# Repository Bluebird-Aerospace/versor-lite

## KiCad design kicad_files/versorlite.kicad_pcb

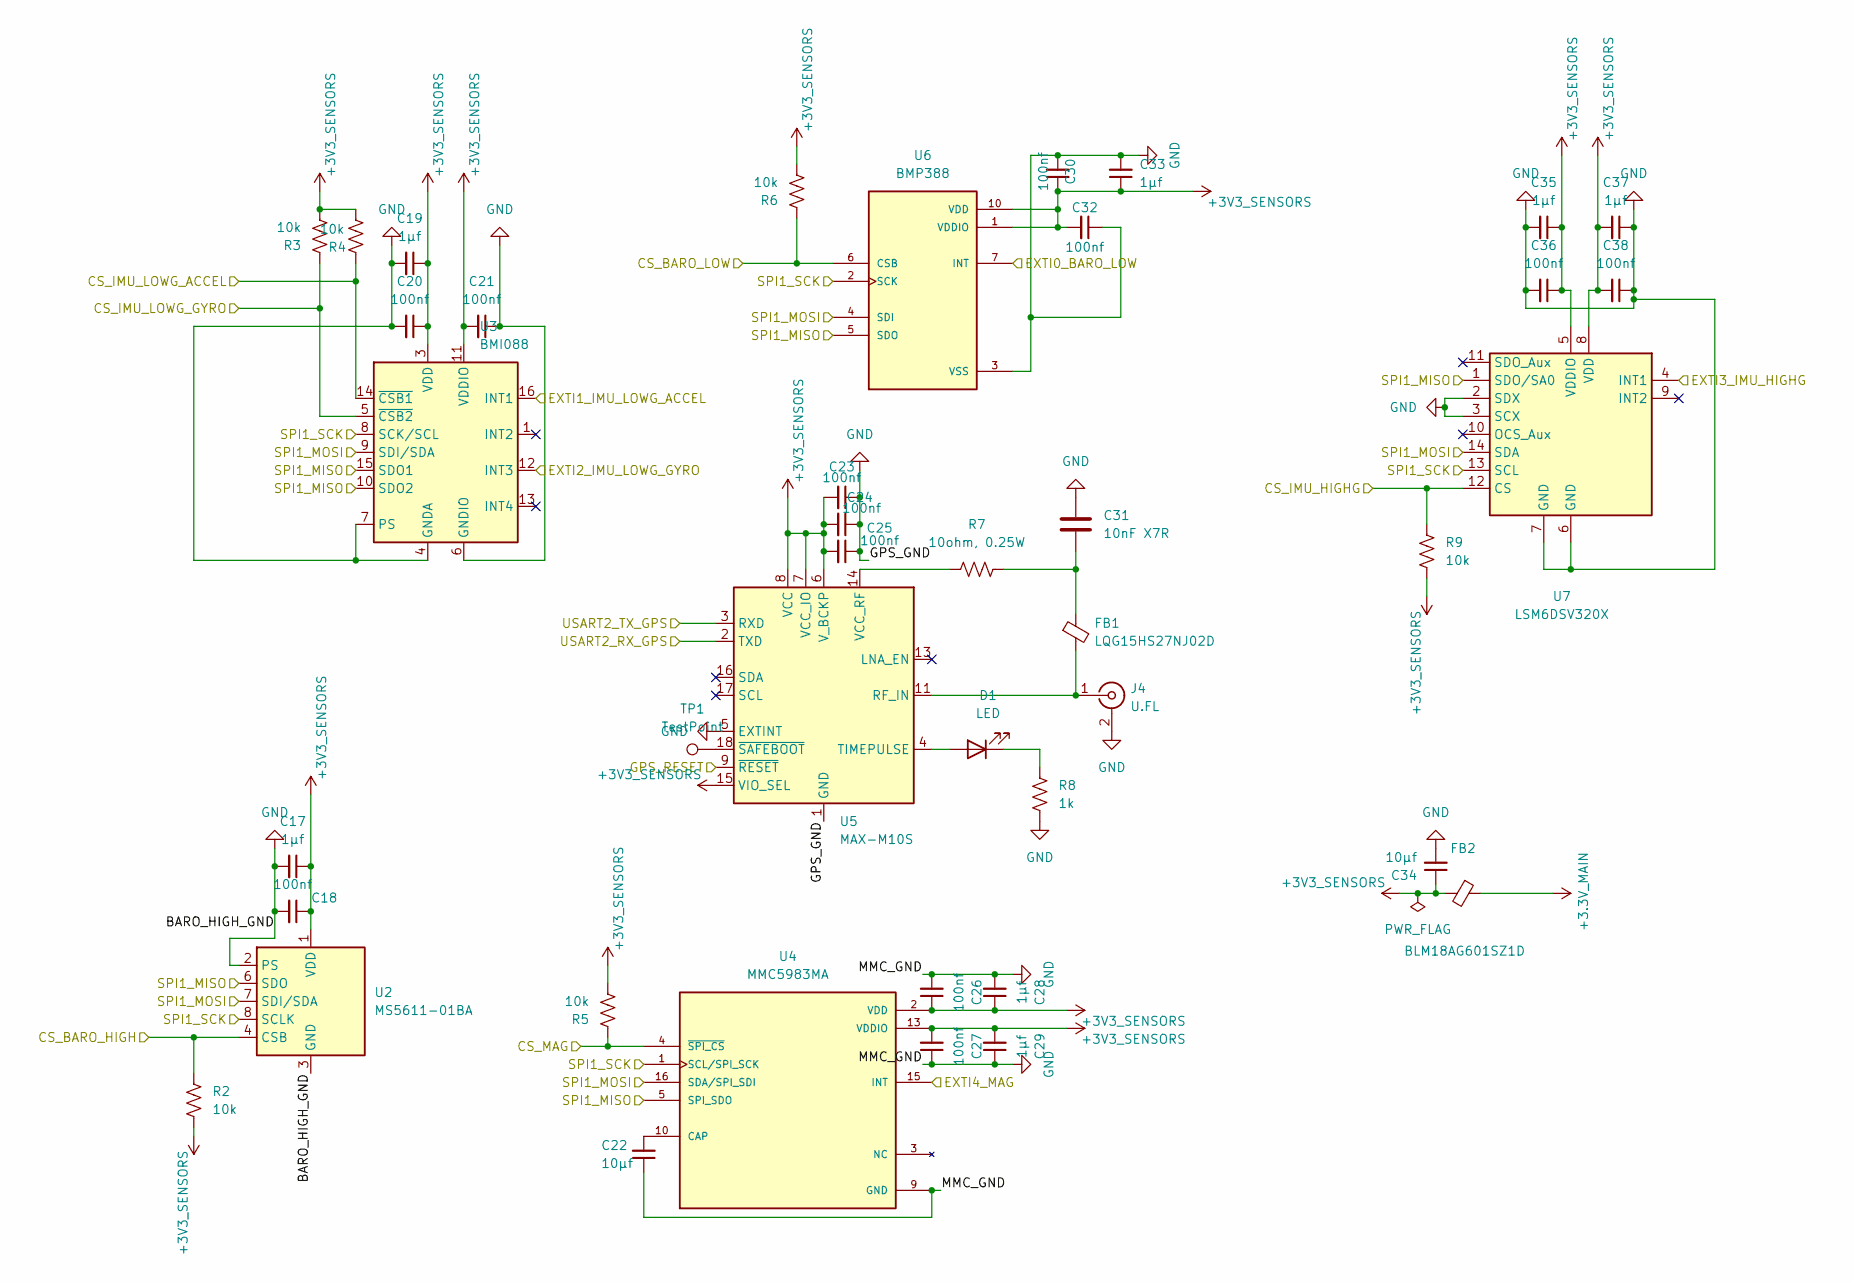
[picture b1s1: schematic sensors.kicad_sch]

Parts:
C17, C19, C28, C29, C33, C35, C37: 1μf; C_0402_1005Metric
C18, C20, C21, C23, C24, C25, C26, C27, C30, C32, C36, C38: 100nf; C_0402_1005Metric
C22, C34: 10μf; C_0805_2012Metric
C31: 10nF X7R; C_0402_1005Metric
D1: LED; LED_0603_1608Metric
FB1: LQG15HS27NJ02D; L_0402_1005Metric
FB2: BLM18AG601SZ1D; L_0603_1608Metric
J4: U.FL; U.FL_Hirose_U.FL-R-SMT-1_Vertical; LCSC C5137195
R2, R3, R4, R5, R6, R9: 10k; R_0402_1005Metric
R7: 10ohm, 0.25W; R_1206_3216Metric
R8: 1k; R_0603_1608Metric
TP1: TestPoint; TestPoint_Pad_D1.0mm
U2: MS5611-01BA; LGA-8_3x5mm_P1.25mm
U3: BMI088; Bosch_LGA-16_4.5x3mm_P0.5mm_LayoutBorder7x1y_ClockwisePinNu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
U4: MMC5983MA; PQFN50P300X300X100-16N; PARTREV A
U5: MAX-M10S; ublox_MAX
U6: BMP388; PARTREV 1.1
U7: LSM6DSV320X; LGA-14_3x2.5mm_P0.5mm_LayoutBorder3x4y

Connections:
+3.3V_MAIN: FB2.1; also elsewhere on the board
+3V3_SENSORS: C17.1, C18.1, C19.1, C20.1, C21.2, C23.2, C24.2, C25.2, C26.1, C27.2, C28.1, C29.2, C30.1, C32.2, C33.1, C34.1, C35.1, C36.1, C37.2, C38.2, FB2.2, R2.2, R3.2, R4.2, R5.2, R6.2, R9.2, U2.1 (VDD), U3.3 (VDD), U3.11 (VDDIO), U4.2 (VDD), U4.13 (VDDIO), U5.6 (V_BCKP), U5.7 (VCC_IO), U5.8 (VCC), U5.15 (VIO_SEL), U6.1 (VDDIO), U6.10 (VDD), U7.5 (VDDIO), U7.8 (VDD)
/MCU/CS_BARO_HIGH: R2.1, U2.4 (CSB), U2.5 (CSB); also elsewhere on the board
/MCU/CS_BARO_LOW: R6.1, U6.6 (CSB); also elsewhere on the board
/MCU/CS_IMU_HIGHG: R9.1, U7.12 (CS); also elsewhere on the board
/MCU/CS_IMU_LOWG_ACCEL: R4.1, U3.14 (~CSB1); also elsewhere on the board
/MCU/CS_IMU_LOWG_GYRO: R3.1, U3.5 (~CSB2); also elsewhere on the board
/MCU/CS_MAG: R5.1, U4.4 (~SPI_CS); also elsewhere on the board
/MCU/EXTI0_BARO_LOW: U6.7 (INT); also elsewhere on the board
/MCU/EXTI1_IMU_LOWG_ACCEL: U3.16 (INT1); also elsewhere on the board
/MCU/EXTI2_IMU_LOWG_GYRO: U3.12 (INT3); also elsewhere on the board
/MCU/EXTI3_IMU_HIGHG: U7.4 (INT1); also elsewhere on the board
/MCU/EXTI4_MAG: U4.15 (INT); also elsewhere on the board
/MCU/GPS_RESET: U5.9 (~RESET); also elsewhere on the board
/MCU/SPI1_MISO: U2.6 (SDO), U3.10 (SDO2), U3.15 (SDO1), U4.5 (SPI_SDO), U6.5 (SDO), U7.1 (SDO/SA0); also elsewhere on the board
/MCU/SPI1_MOSI: U2.7 (SDI/SDA), U3.9 (SDI/SDA), U4.16 (SDA/SPI_SDI), U6.4 (SDI), U7.14 (SDA); also elsewhere on the board
/MCU/SPI1_SCK: U2.8 (SCLK), U3.8 (SCK/SCL), U4.1 (SCL/SPI_SCK), U6.2 (SCK), U7.13 (SCL); also elsewhere on the board
/MCU/USART2_RX_GPS: U5.2 (TXD); also elsewhere on the board
/MCU/USART2_TX_GPS: U5.3 (RXD); also elsewhere on the board
GND: C17.2, C18.2, C19.2, C20.2, C21.1, C22.1, C23.1, C24.1, C25.1, C26.2, C27.1, C28.2, C29.1, C30.2, C31.1, C32.1, C33.2, C34.2, C35.2, C36.2, C37.1, C38.1, J4.2 (Ext), R8.2, U2.2 (PS), U2.3 (GND), U3.2 (GNDA), U3.4 (GNDA), U3.6 (GNDIO), U3.7 (PS), U4.9 (GND), U4.11 (GND), U5.1 (GND), U5.5 (EXTINT), U5.10 (GND), U5.12 (GND), U6.3 (VSS), U6.8 (VSS), U6.9 (VSS), U7.2 (SDX), U7.3 (SCX), U7.6 (GND), U7.7 (GND); also elsewhere on the board
unnamed: C31.2, FB1.1, R7.2
unnamed: D1.2 (A), U5.4 (TIMEPULSE)
unnamed: D1.1 (K), R8.1
unnamed: FB1.2, J4.1 (In), U5.11 (RF_IN)
unnamed: C22.2, U4.10 (CAP)
unnamed: R7.1, U5.14 (VCC_RF)
unnamed: TP1.1 (1_1), U5.18 (~SAFEBOOT)

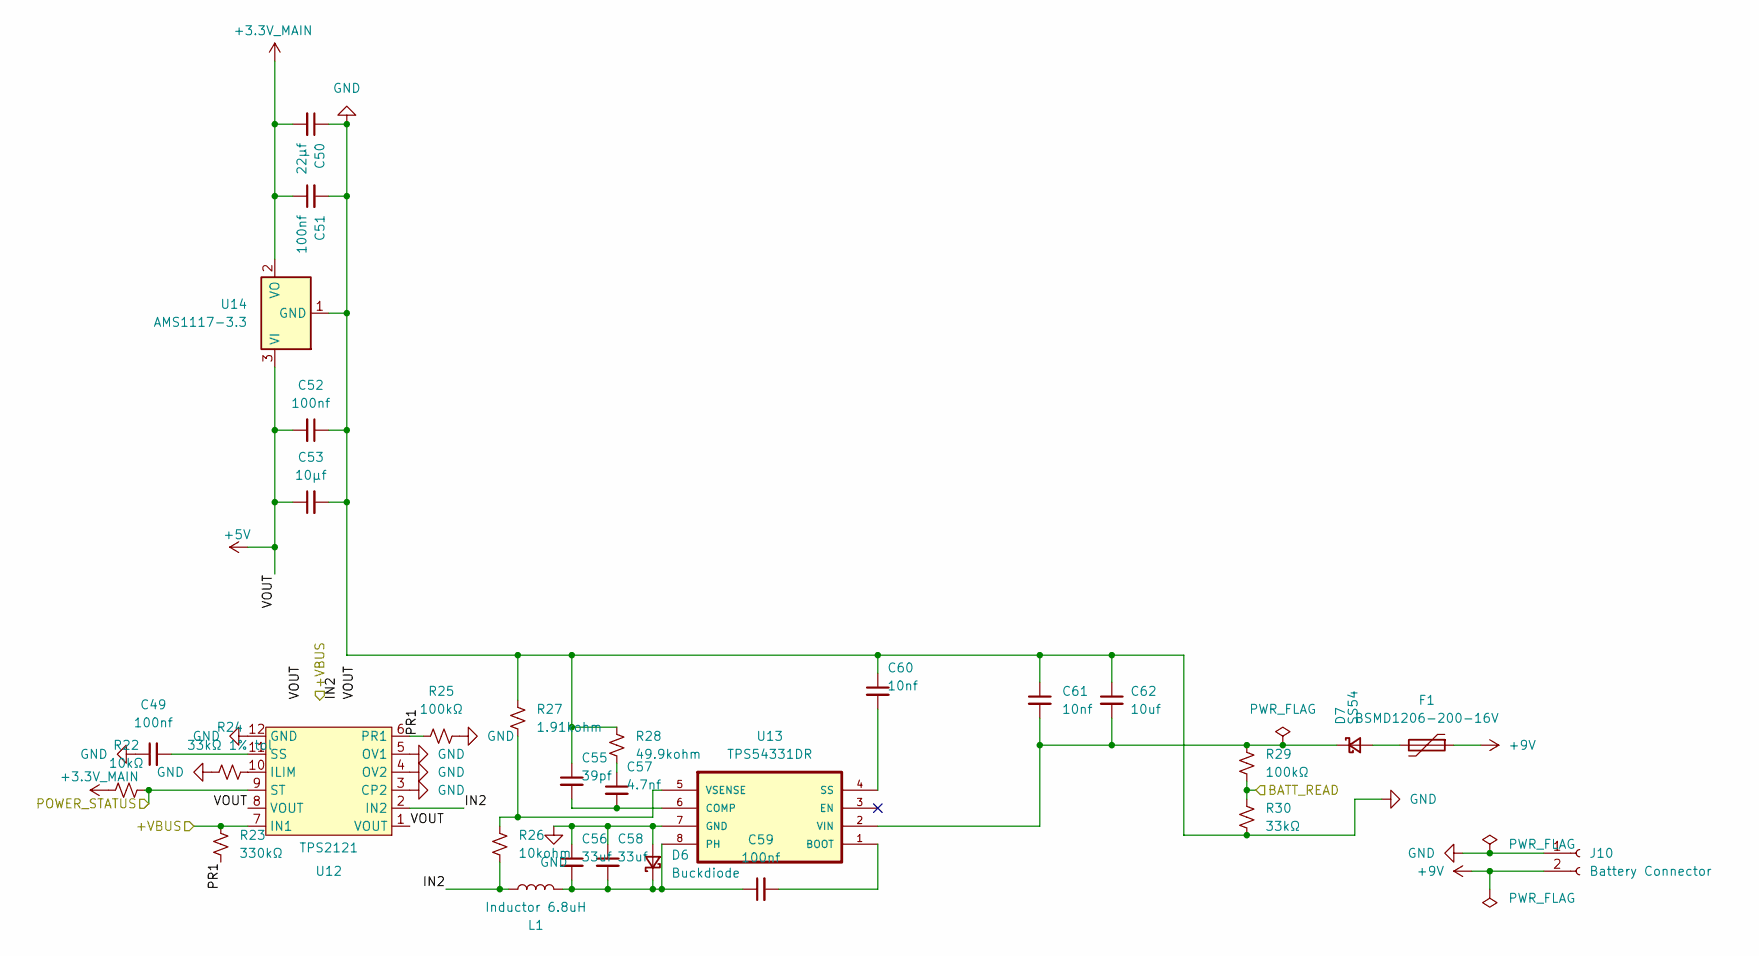
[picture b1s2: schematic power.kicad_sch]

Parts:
C49, C51, C52, C59: 100nf; C_0402_1005Metric
C50: 22μf; C_0805_2012Metric
C53: 10μf; C_0805_2012Metric
C55: 39pf; C_0402_1005Metric
C56, C58: 33uf; C_0805_2012Metric
C57: 4.7nf; C_0402_1005Metric
C60, C61: 10nf; C_0402_1005Metric
C62: 10uf; C_0805_2012Metric
D6: Buckdiode; D_SMA
D7: SS54; D_SMA
F1: BSMD1206-200-16V; Fuse_1206_3216Metric
J10: Battery Connector; AMASS_XT30U-F_1x02_P5.0mm_Vertical
L1: Inductor 6.8uH; L_Coilcraft_XxL4030
R22: 10kΩ; R_0402_1005Metric
R23: 330kΩ; R_0402_1005Metric
R24: 33kΩ 1% tol; R_0402_1005Metric
R25: 100kΩ; R_0402_1005Metric
R26: 10kohm; R_0402_1005Metric
R27: 1.91kohm; R_0402_1005Metric
R28: 49.9kohm; R_0402_1005Metric
R29: 100kΩ; R_0603_1608Metric
R30: 33kΩ; R_0603_1608Metric
U12: TPS2121; IC_TPS2121RUXR
U13: TPS54331DR; SOIC127P599X175-8N
U14: AMS1117-3.3; SOT-223-3_TabPin2

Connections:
+3.3V_MAIN: C50.2, C51.1, R22.1, U14.2 (VO); also elsewhere on the board
+5V: C52.2, C53.1, U12.1 (VOUT), U12.1_1 (TV), U12.8 (VOUT), U12.8_1 (TV), U14.3 (VI); also elsewhere on the board
+9V: F1.1, J10.2; also elsewhere on the board
/MCU/BATT_READ: R29.2, R30.1; also elsewhere on the board
/MCU/POWER_STATUS: R22.2, U12.9 (ST); also elsewhere on the board
/Power/+VBUS: R23.2, U12.7 (IN1), U12.7_1 (TV); also elsewhere on the board
/Power/IN2: L1.1, R26.2, U12.2 (IN2), U12.2_1 (TV)
/Power/PR1: R23.1, R25.1, U12.6 (PR1)
GND: C49.1, C50.1, C51.2, C52.1, C53.2, C55.1, C56.1, C58.1, C60.1, C61.1, C62.1, D6.2 (A), J10.1, R24.1, R25.2, R27.1, R28.1, R30.2, U12.3 (CP2), U12.4 (OV2), U12.5 (OV1), U12.12 (GND), U13.7 (GND), U14.1 (GND); also elsewhere on the board
unnamed: C57.1, R28.2
unnamed: C56.2, C58.2, C59.1, D6.1 (K), L1.2, U13.8 (PH)
unnamed: D7.2 (A), F1.2
unnamed: C61.2, C62.2, D7.1 (K), R29.1, U13.2 (VIN)
unnamed: R24.2, U12.10 (ILIM)
unnamed: C49.2, U12.11 (SS)
unnamed: C59.2, U13.1 (BOOT)
unnamed: C55.2, C57.2, U13.6 (COMP)
unnamed: C60.2, U13.4 (SS)
unnamed: R26.1, R27.2, U13.5 (VSENSE)

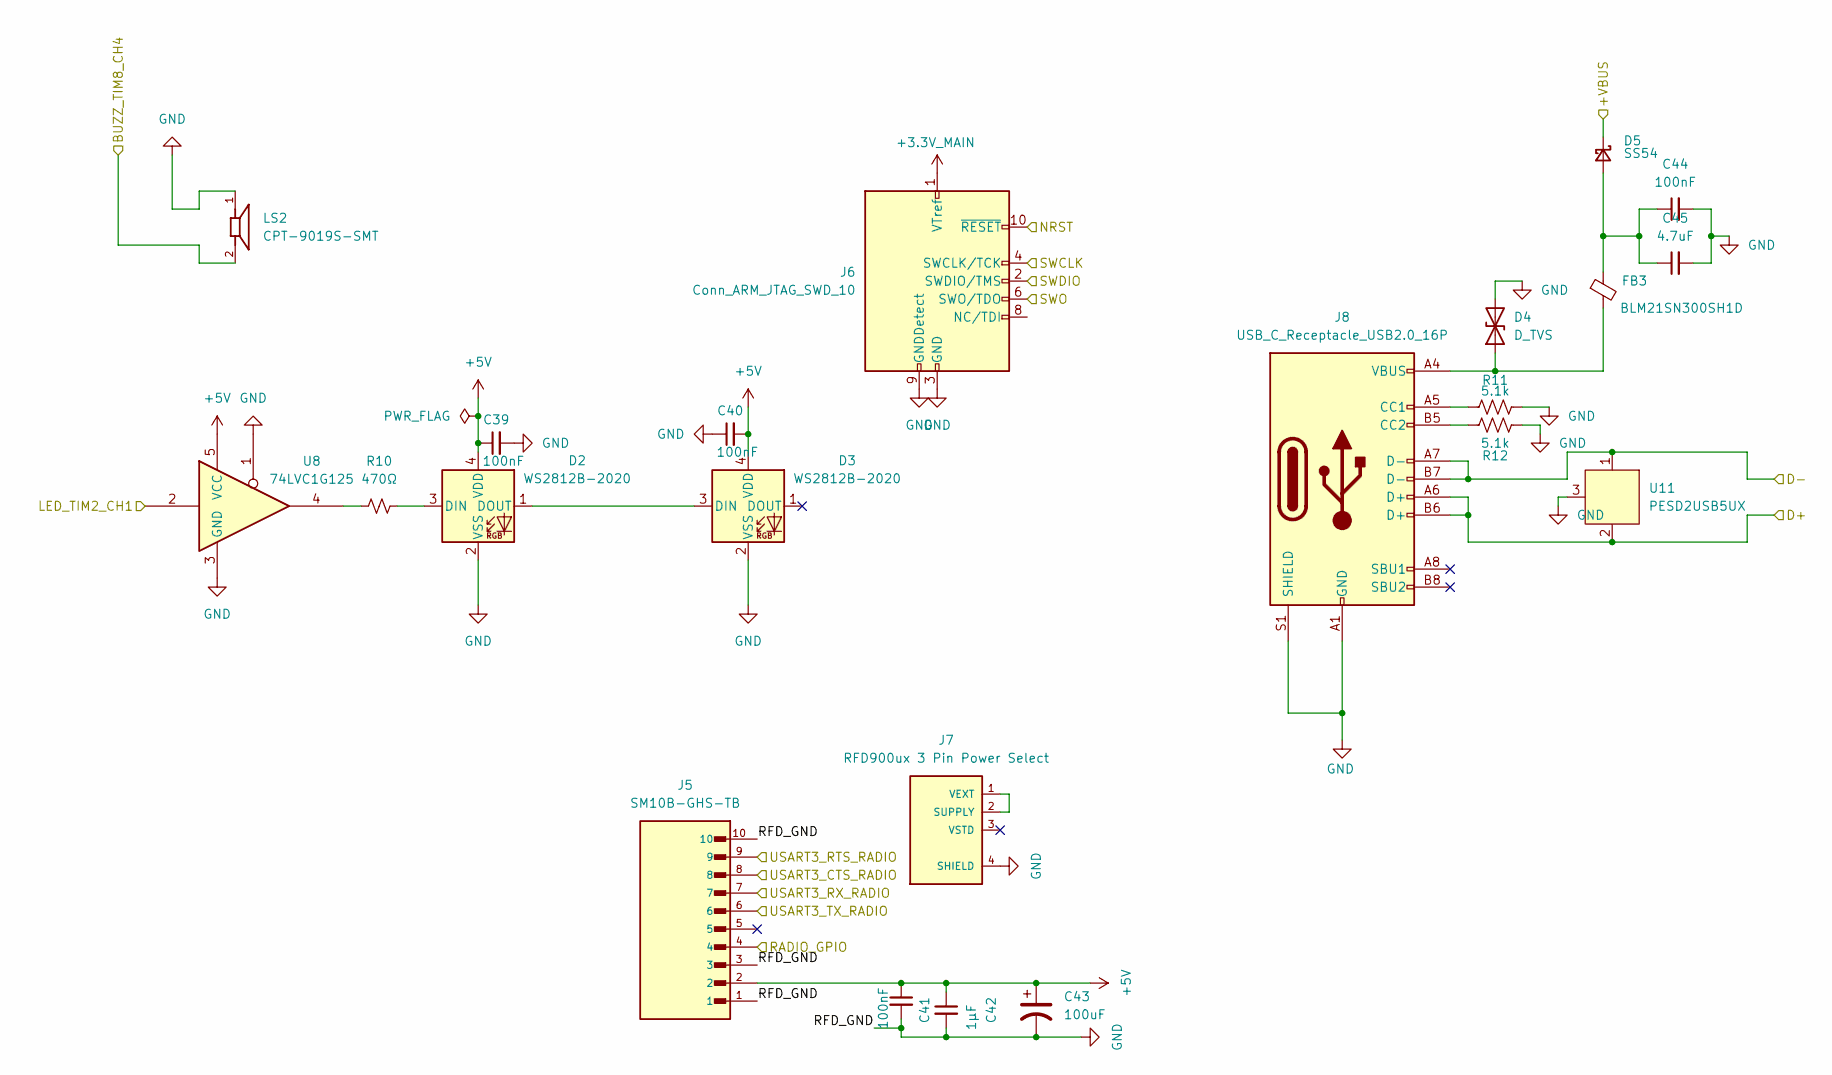
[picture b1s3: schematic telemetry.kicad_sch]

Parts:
C39, C40, C41, C44: 100nF; C_0402_1005Metric
C42: 1μF; C_0402_1005Metric
C43: 100uF; CP_EIA-3528-21_Kemet-B
C45: 4.7uF; C_0603_1608Metric
D2, D3: WS2812B-2020; LED_WS2812B-2020_PLCC4_2.0x2.0mm
D4: D_TVS; D_SOD-882
D5: SS54; D_SMA
FB3: BLM21SN300SH1D; L_0805_2012Metric
J5: SM10B-GHS-TB; JST_SM10B-GHS-TB
J6: Conn_ARM_JTAG_SWD_10; PinHeader_2x05_P1.27mm_Vertical
J7: RFD900ux 3 Pin Power Select; CONN_BM03B-GHS-TBT_LF__SN__N_
J8: USB_C_Receptacle_USB2.0_16P; USB_C_Receptacle_GCT_USB4105-xx-A_16P_TopMnt_Horizontal
LS2: CPT-9019S-SMT; CUI_CPT-9019S-SMT; PART_REV 1.0
R10: 470Ω; R_0402_1005Metric
R11, R12: 5.1k; R_0402_1005Metric
U8: 74LVC1G125; SOT-23-5
U11: PESD2USB5UX; TSOT-23

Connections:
+3.3V_MAIN: J6.1 (VTref); also elsewhere on the board
+5V: C39.1, C40.2, C41.1, C42.1, C43.1, D2.4 (VDD), D3.4 (VDD), J5.2, U8.5 (VCC); also elsewhere on the board
/MCU/BUZZ_TIM8_CH4: LS2.2; also elsewhere on the board
/MCU/D+: J8.A6 (D+), J8.B6 (D+), U11.2; also elsewhere on the board
/MCU/D-: J8.A7 (D-), J8.B7 (D-), U11.1; also elsewhere on the board
/MCU/LED_TIM2_CH1: U8.2; also elsewhere on the board
/MCU/NRST: J6.10 (~RESET); also elsewhere on the board
/MCU/RADIO_GPIO: J5.4; also elsewhere on the board
/MCU/SWCLK: J6.4 (SWCLK/TCK); also elsewhere on the board
/MCU/SWDIO: J6.2 (SWDIO/TMS); also elsewhere on the board
/MCU/SWO: J6.6 (SWO/TDO); also elsewhere on the board
/MCU/USART3_CTS_RADIO: J5.8; also elsewhere on the board
/MCU/USART3_RTS_RADIO: J5.9; also elsewhere on the board
/MCU/USART3_RX_RADIO: J5.7; also elsewhere on the board
/MCU/USART3_TX_RADIO: J5.6; also elsewhere on the board
/Power/+VBUS: D5.1 (K); also elsewhere on the board
GND: C39.2, C40.1, C41.2, C42.2, C43.2, C44.2, C45.2, D2.2 (VSS), D3.2 (VSS), D4.2 (A2), J5.1, J5.3, J5.10, J6.3 (GND), J6.5 (GND), J6.9 (GNDDetect), J7.4 (SHIELD), J7.5 (SHIELD), J8.A1 (GND), J8.A12 (GND), J8.B1 (GND), J8.B12 (GND), J8.S1 (SHIELD), LS2.1, R11.2, R12.2, U8.1, U8.3 (GND), U11.3; also elsewhere on the board
unnamed: D2.3 (DIN), R10.2
unnamed: D2.1 (DOUT), D3.3 (DIN)
unnamed: D4.1 (A1), FB3.2, J8.A4 (VBUS), J8.A9 (VBUS), J8.B4 (VBUS), J8.B9 (VBUS)
unnamed: C44.1, C45.1, D5.2 (A), FB3.1
unnamed: J7.1 (VEXT), J7.2 (SUPPLY)
unnamed: J8.A5 (CC1), R11.1
unnamed: J8.B5 (CC2), R12.1
unnamed: R10.1, U8.4

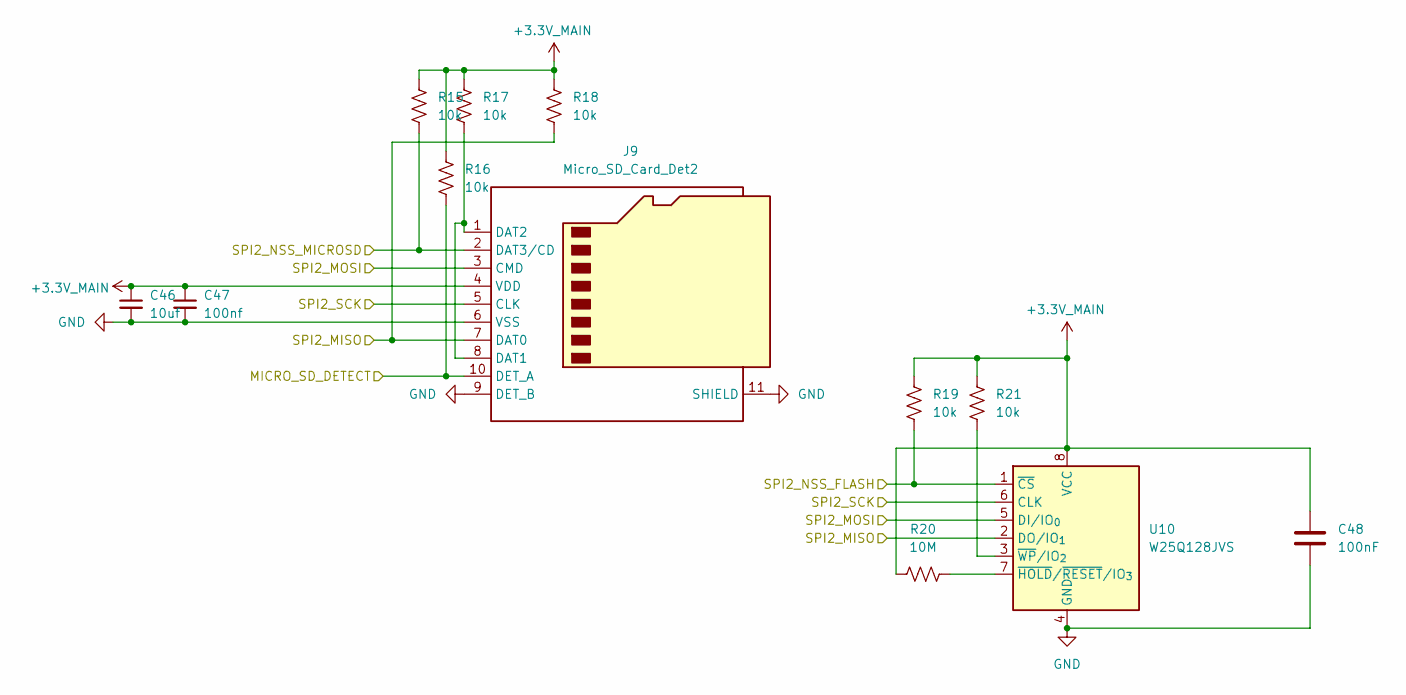
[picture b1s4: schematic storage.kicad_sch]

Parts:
C46: 10uf; C_0805_2012Metric
C47: 100nf; C_0402_1005Metric
C48: 100nF; C_0402_1005Metric
J9: Micro_SD_Card_Det2; microSD_HC_Molex_104031-0811
R15, R16, R17, R18, R19, R21: 10k; R_0402_1005Metric
R20: 10M; R_0603_1608Metric
U10: W25Q128JVS; SOIC-8_5.3x5.3mm_P1.27mm

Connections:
+3.3V_MAIN: C46.1, C47.1, C48.1, J9.4 (VDD), R15.1, R16.1, R17.2, R18.2, R19.1, R20.1, R21.1, U10.8 (VCC); also elsewhere on the board
/MCU/MICRO_SD_DETECT: J9.10 (DET_A), R16.2; also elsewhere on the board
/MCU/SPI2_MISO: J9.7 (DAT0), R18.1, U10.2 (DO/IO_{1}); also elsewhere on the board
/MCU/SPI2_MOSI: J9.3 (CMD), U10.5 (DI/IO_{0}); also elsewhere on the board
/MCU/SPI2_NSS_FLASH: R19.2, U10.1 (~CS); also elsewhere on the board
/MCU/SPI2_NSS_MICROSD: J9.2 (DAT3/CD), R15.2; also elsewhere on the board
/MCU/SPI2_SCK: J9.5 (CLK), U10.6 (CLK); also elsewhere on the board
GND: C46.2, C47.2, C48.2, J9.6 (VSS), J9.9 (DET_B), J9.11 (SHIELD), U10.4 (GND); also elsewhere on the board
unnamed: J9.1 (DAT2), J9.8 (DAT1), R17.1
unnamed: R20.2, U10.7 (~HOLD/~RESET/IO_{3})
unnamed: R21.2, U10.3 (~WP/IO_{2})

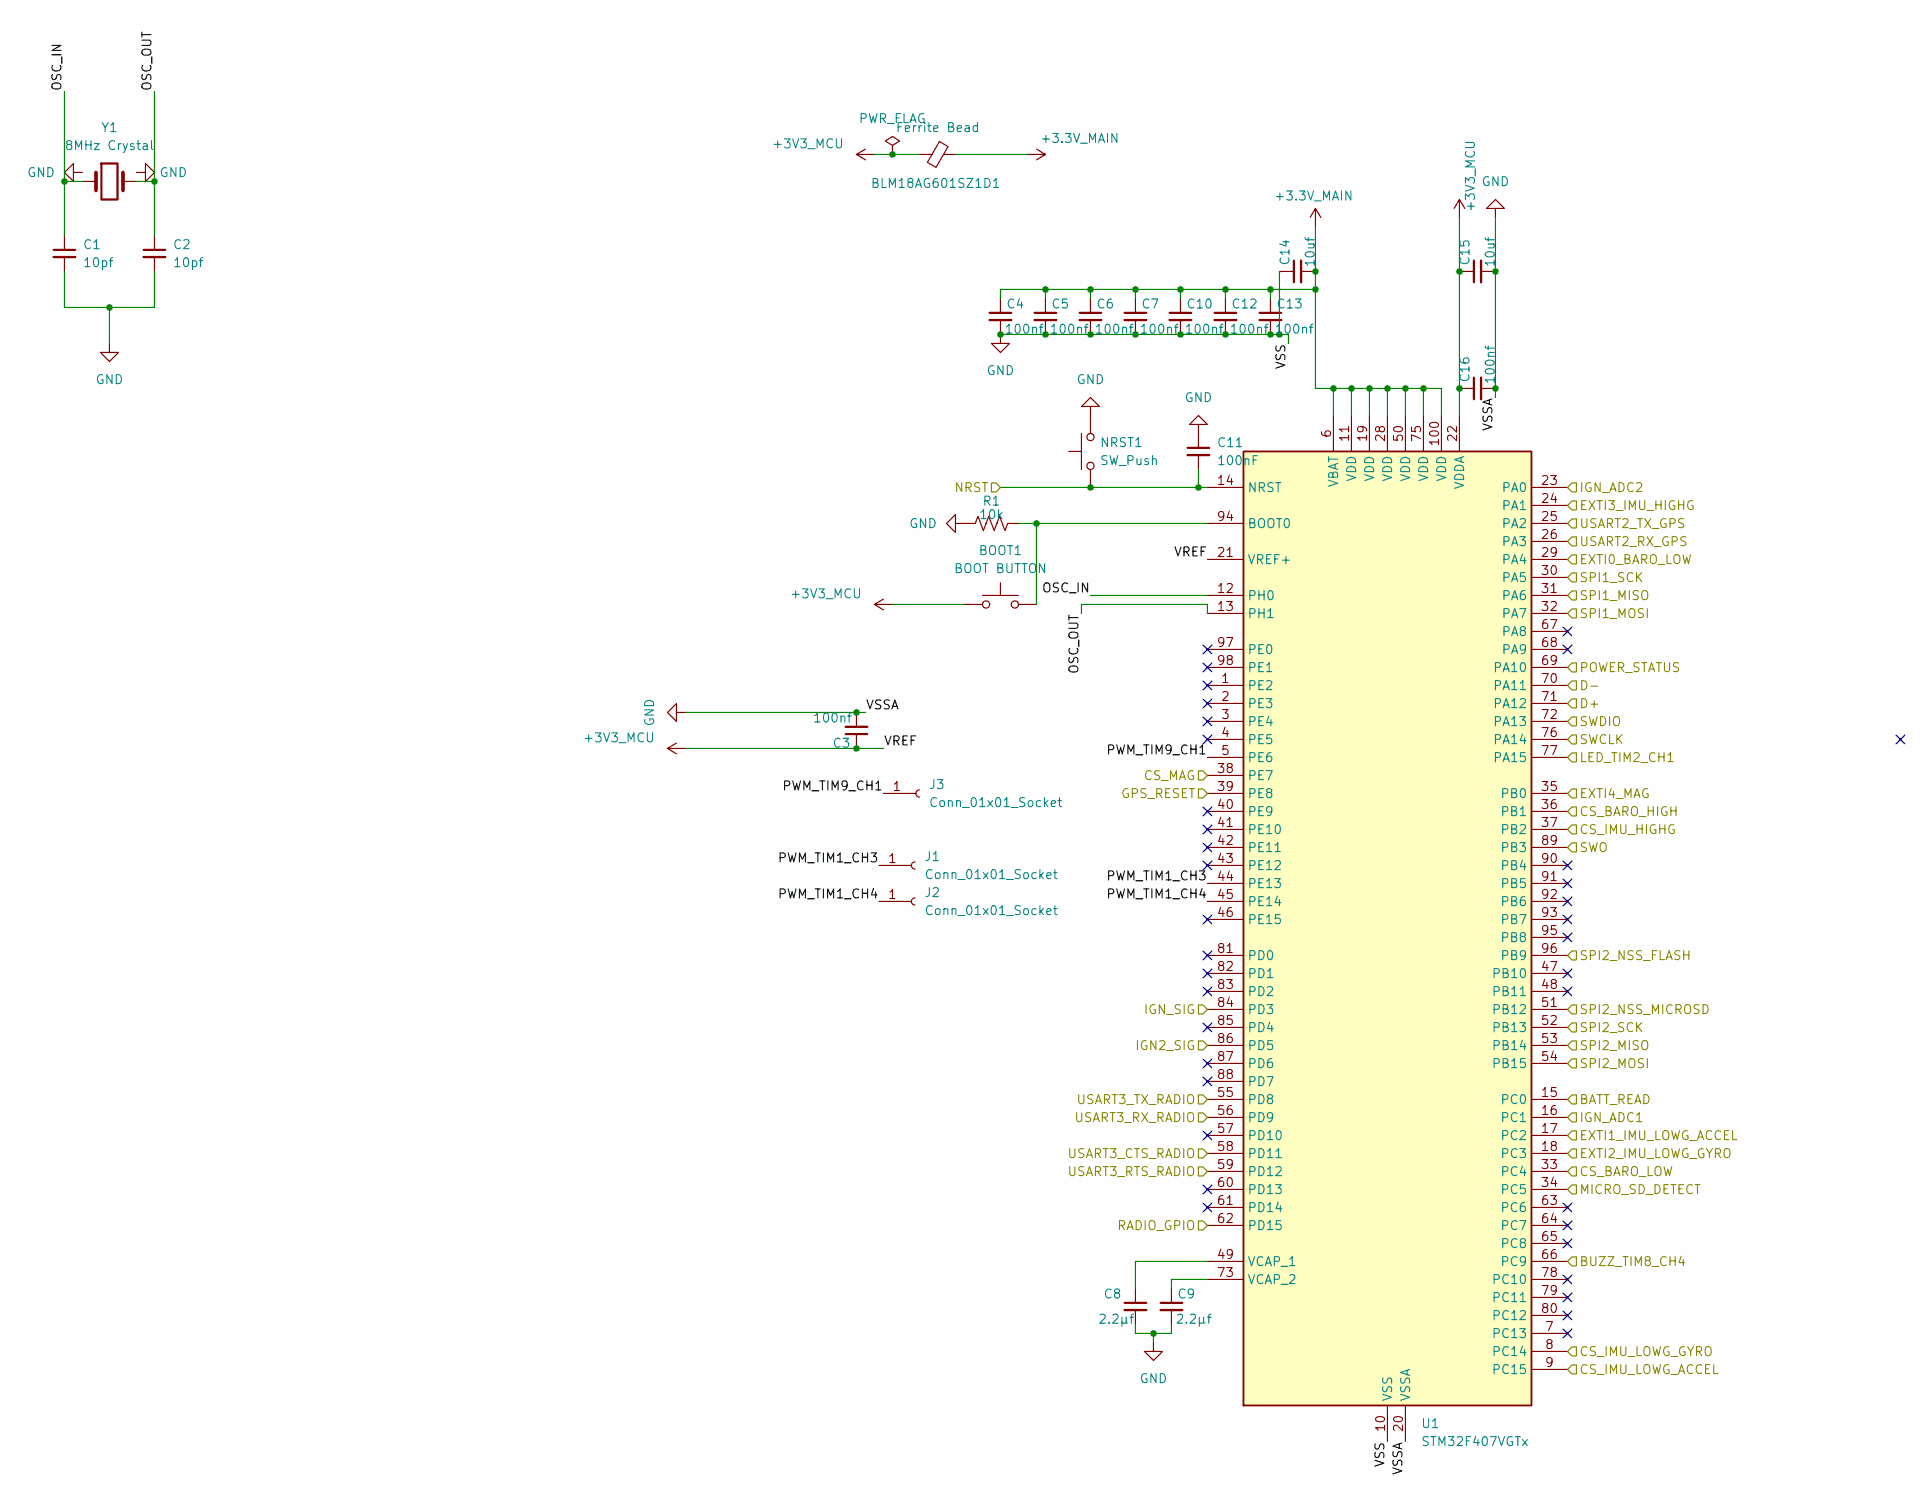
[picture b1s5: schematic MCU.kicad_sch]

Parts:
BLM18AG601SZ1D1: Ferrite Bead; L_0603_1608Metric
BOOT1: BOOT BUTTON; SW_SPST_PTS810
C1, C2: 10pf; C_0402_1005Metric
C3, C4, C5, C6, C7, C10, C12, C13, C16: 100nf; C_0402_1005Metric
C8, C9: 2.2µf; C_0603_1608Metric
C11: 100nF; C_0402_1005Metric
C14, C15: 10uf; C_0805_2012Metric
J1, J2, J3: Conn_01x01_Socket; SolderWire-0.5sqmm_1x01_D0.9mm_OD2.1mm
NRST1: SW_Push; SW_SPST_PTS810
R1: 10k; R_0402_1005Metric
U1: STM32F407VGTx; LQFP-100_14x14mm_P0.5mm
Y1: 8MHz Crystal; Crystal_SMD_3225-4Pin_3.2x2.5mm

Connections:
+3.3V_MAIN: BLM18AG601SZ1D1.1, C4.1, C5.1, C6.1, C7.1, C10.1, C12.1, C13.1, C14.2, U1.6 (VBAT), U1.11 (VDD), U1.19 (VDD), U1.28 (VDD), U1.50 (VDD), U1.75 (VDD), U1.100 (VDD); also elsewhere on the board
+3V3_MCU: BLM18AG601SZ1D1.2, BOOT1.1, C3.1, C15.1, C16.1, U1.21 (VREF+), U1.22 (VDDA)
/MCU/BATT_READ: U1.15 (PC0); also elsewhere on the board
/MCU/BUZZ_TIM8_CH4: U1.66 (PC9); also elsewhere on the board
/MCU/CS_BARO_HIGH: U1.36 (PB1); also elsewhere on the board
/MCU/CS_BARO_LOW: U1.33 (PC4); also elsewhere on the board
/MCU/CS_IMU_HIGHG: U1.37 (PB2); also elsewhere on the board
/MCU/CS_IMU_LOWG_ACCEL: U1.9 (PC15); also elsewhere on the board
/MCU/CS_IMU_LOWG_GYRO: U1.8 (PC14); also elsewhere on the board
/MCU/CS_MAG: U1.38 (PE7); also elsewhere on the board
/MCU/D+: U1.71 (PA12); also elsewhere on the board
/MCU/D-: U1.70 (PA11); also elsewhere on the board
/MCU/EXTI0_BARO_LOW: U1.29 (PA4); also elsewhere on the board
/MCU/EXTI1_IMU_LOWG_ACCEL: U1.17 (PC2); also elsewhere on the board
/MCU/EXTI2_IMU_LOWG_GYRO: U1.18 (PC3); also elsewhere on the board
/MCU/EXTI3_IMU_HIGHG: U1.24 (PA1); also elsewhere on the board
/MCU/EXTI4_MAG: U1.35 (PB0); also elsewhere on the board
/MCU/GPS_RESET: U1.39 (PE8); also elsewhere on the board
/MCU/IGN2_SIG: U1.86 (PD5); also elsewhere on the board
/MCU/IGN_ADC1: U1.16 (PC1); also elsewhere on the board
/MCU/IGN_ADC2: U1.23 (PA0); also elsewhere on the board
/MCU/IGN_SIG: U1.84 (PD3); also elsewhere on the board
/MCU/LED_TIM2_CH1: U1.77 (PA15); also elsewhere on the board
/MCU/MICRO_SD_DETECT: U1.34 (PC5); also elsewhere on the board
/MCU/NRST: C11.2, NRST1.1, U1.14 (NRST); also elsewhere on the board
/MCU/OSC_IN: C1.1, U1.12 (PH0), Y1.1
/MCU/OSC_OUT: C2.1, U1.13 (PH1), Y1.3
/MCU/POWER_STATUS: U1.69 (PA10); also elsewhere on the board
/MCU/PWM_TIM1_CH3: J1.1 (Pin_1_1), U1.44 (PE13)
/MCU/PWM_TIM1_CH4: J2.1 (Pin_1_1), U1.45 (PE14)
/MCU/PWM_TIM9_CH1: J3.1 (Pin_1_1), U1.5 (PE6)
/MCU/RADIO_GPIO: U1.62 (PD15); also elsewhere on the board
/MCU/SPI1_MISO: U1.31 (PA6); also elsewhere on the board
/MCU/SPI1_MOSI: U1.32 (PA7); also elsewhere on the board
/MCU/SPI1_SCK: U1.30 (PA5); also elsewhere on the board
/MCU/SPI2_MISO: U1.53 (PB14); also elsewhere on the board
/MCU/SPI2_MOSI: U1.54 (PB15); also elsewhere on the board
/MCU/SPI2_NSS_FLASH: U1.96 (PB9); also elsewhere on the board
/MCU/SPI2_NSS_MICROSD: U1.51 (PB12); also elsewhere on the board
/MCU/SPI2_SCK: U1.52 (PB13); also elsewhere on the board
/MCU/SWCLK: U1.76 (PA14); also elsewhere on the board
/MCU/SWDIO: U1.72 (PA13); also elsewhere on the board
/MCU/SWO: U1.89 (PB3); also elsewhere on the board
/MCU/USART2_RX_GPS: U1.26 (PA3); also elsewhere on the board
/MCU/USART2_TX_GPS: U1.25 (PA2); also elsewhere on the board
/MCU/USART3_CTS_RADIO: U1.58 (PD11); also elsewhere on the board
/MCU/USART3_RTS_RADIO: U1.59 (PD12); also elsewhere on the board
/MCU/USART3_RX_RADIO: U1.56 (PD9); also elsewhere on the board
/MCU/USART3_TX_RADIO: U1.55 (PD8); also elsewhere on the board
GND: C1.2, C2.2, C3.2, C4.2, C5.2, C6.2, C7.2, C8.2, C9.2, C10.2, C11.1, C12.2, C13.2, C14.1, C15.2, C16.2, NRST1.2, R1.1, U1.10 (VSS), U1.20 (VSSA), U1.27 (VSS), U1.74 (VSS), U1.99 (VSS), Y1.2, Y1.4; also elsewhere on the board
unnamed: BOOT1.2, R1.2, U1.94 (BOOT0)
unnamed: C8.1, U1.49 (VCAP_1)
unnamed: C9.1, U1.73 (VCAP_2)

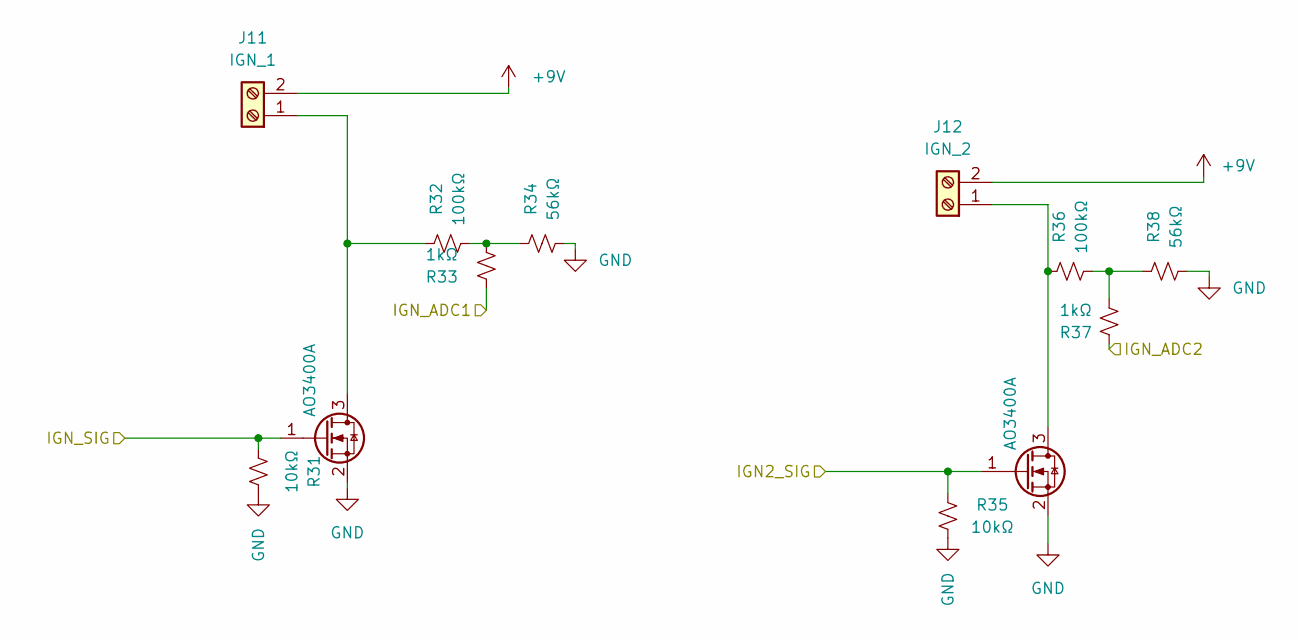
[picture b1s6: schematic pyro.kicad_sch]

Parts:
J11: IGN_1; SolderWire-0.5sqmm_1x02_P4.6mm_D0.9mm_OD2.1mm
J12: IGN_2; SolderWire-0.5sqmm_1x02_P4.6mm_D0.9mm_OD2.1mm
Q1, Q2: AO3400A; SOT-23
R31, R35: 10kΩ; R_0402_1005Metric
R32, R36: 100kΩ; R_0402_1005Metric
R33, R37: 1kΩ; R_0402_1005Metric
R34, R38: 56kΩ; R_0402_1005Metric

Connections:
+9V: J11.2, J12.2; also elsewhere on the board
/MCU/IGN2_SIG: Q2.1 (G), R35.1; also elsewhere on the board
/MCU/IGN_ADC1: R33.1; also elsewhere on the board
/MCU/IGN_ADC2: R37.1; also elsewhere on the board
/MCU/IGN_SIG: Q1.1 (G), R31.1; also elsewhere on the board
GND: Q1.2 (S), Q2.2 (S), R31.2, R34.2, R35.2, R38.2; also elsewhere on the board
unnamed: J11.1, Q1.3 (D), R32.1
unnamed: J12.1, Q2.3 (D), R36.1
unnamed: R32.2, R33.2, R34.1
unnamed: R36.2, R37.2, R38.1

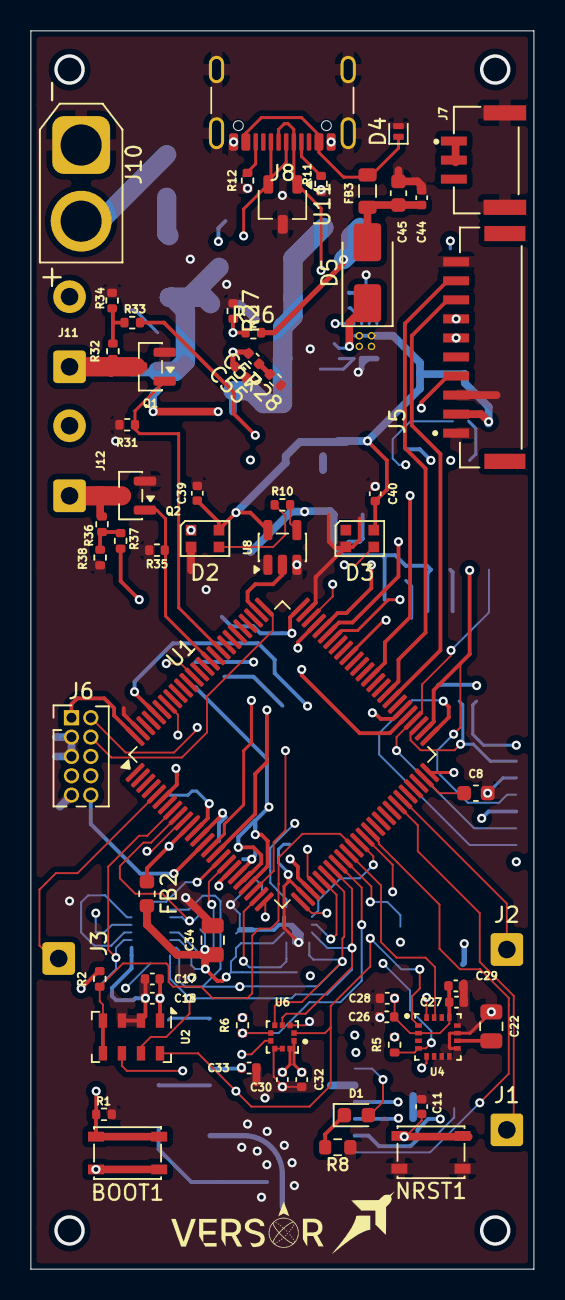
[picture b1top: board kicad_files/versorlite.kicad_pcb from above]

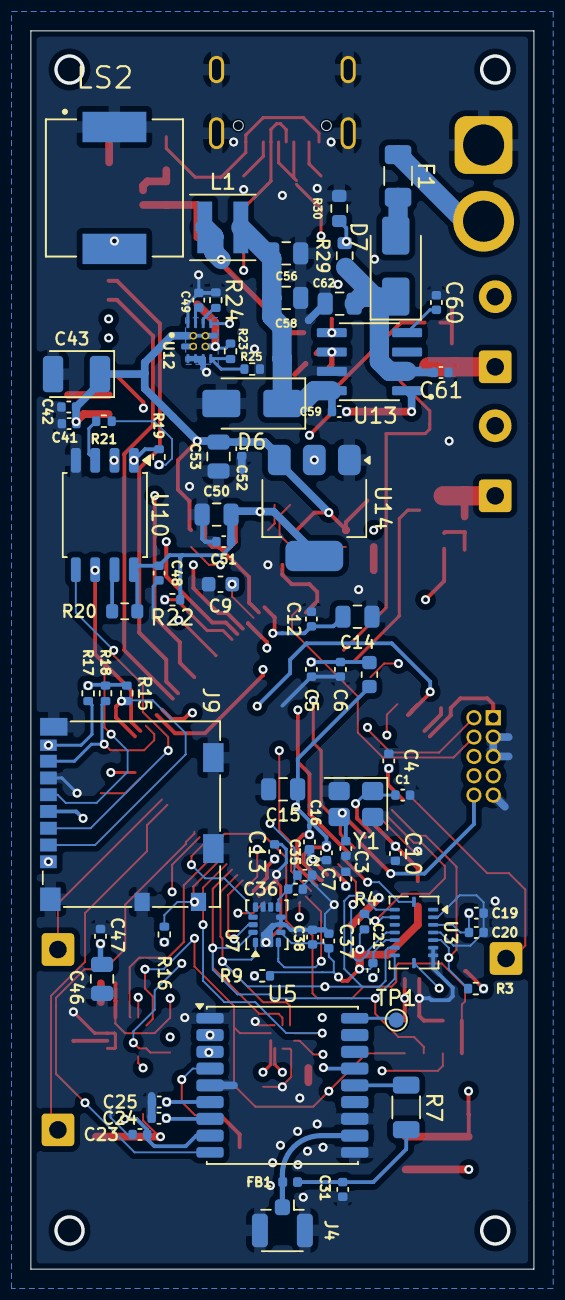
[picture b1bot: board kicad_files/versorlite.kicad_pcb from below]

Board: 4 copper layers, 33.0 x 81.3 mm, 142 parts (77 on the bottom side), 91 nets.

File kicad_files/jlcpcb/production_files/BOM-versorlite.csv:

Comment,Designator,Footprint,LCSC,Quantity
1.91kohm,R27,R_0402_1005Metric,C102860,1
100kΩ,"R25,R32,R36",R_0402_1005Metric,C25741,3
100kΩ,R29,R_0603_1608Metric,C25803,1
100nF,"C11,C39,C40,C41,C44,C48",C_0402_1005Metric,C1525,6
100nf,"C10,C12,C13,C16,C18,C20,C21,C23,C24,C25,C26,C27,C3,C30,C32,C36,C38,C4,C47,C49,C5,C51,C52,C59,C6,C7",C_0402_1005Metric,C1525,26
100uF,C43,CP_EIA-3528-21_Kemet-B,C7196,1
10M,R20,R_0603_1608Metric,C7250,1
10k,"R1,R15,R16,R17,R18,R19,R2,R21,R3,R4,R5,R6,R9",R_0402_1005Metric,C25744,13
10kohm,R26,R_0402_1005Metric,C25744,1
10kΩ,"R22,R31,R35",R_0402_1005Metric,C25744,3
10nF X7R,C31,C_0402_1005Metric,C15195,1
10nf,"C60,C61",C_0402_1005Metric,C15195,2
"10ohm, 0.25W",R7,R_1206_3216Metric,C17903,1
10pf,"C1,C2",C_0402_1005Metric,C32949,2
10uf,"C14,C15,C46,C62",C_0805_2012Metric,C15850,4
10μf,"C22,C34,C53",C_0805_2012Metric,C15850,3
1k,R8,R_0603_1608Metric,C21190,1
1kΩ,"R33,R37",R_0402_1005Metric,C11702,2
1μF,C42,C_0402_1005Metric,C52923,1
1μf,"C17,C19,C28,C29,C33,C35,C37",C_0402_1005Metric,C52923,7
2.2µf,"C8,C9",C_0603_1608Metric,C23630,2
22μf,C50,C_0805_2012Metric,C45783,1
330kΩ,R23,R_0402_1005Metric,C25554,1
33kΩ,R30,R_0603_1608Metric,C25779,1
33kΩ 1% tol,R24,R_0402_1005Metric,C25779,1
33uf,"C56,C58",C_0805_2012Metric,C342635,2
39pf,C55,C_0402_1005Metric,C1563,1
4.7nf,C57,C_0402_1005Metric,C1538,1
4.7uF,C45,C_0603_1608Metric,C19666,1
470Ω,R10,R_0402_1005Metric,C25117,1
49.9kohm,R28,R_0402_1005Metric,C137969,1
5.1k,"R11,R12",R_0402_1005Metric,C25905,2
56kΩ,"R34,R38",R_0402_1005Metric,C25567,2
74LVC1G125,U8,SOT-23-5,C23654,1
8MHz Crystal,Y1,Crystal_SMD_3225-4Pin_3.2x2.5mm,C712812,1
AMS1117-3.3,U14,SOT-223-3_TabPin2,C6186,1
AO3400A,"Q1,Q2",SOT-23,C20917,2
BLM18AG601SZ1D,FB2,L_0603_1608Metric,C710353,1
BLM21SN300SH1D,FB3,L_0805_2012Metric,C703137,1
BMI088,U3,Bosch_LGA-16_4.5x3mm_P0.5mm_LayoutBorder7x1y_ClockwisePinNumbering,C194919,1
BMP388,U6,BMP388,C779278,1
BOOT BUTTON,BOOT1,SW_SPST_PTS810,C221895,1
BSMD1206-200-16V,F1,Fuse_1206_3216Metric,C2685749,1
Battery Connector,J10,AMASS_XT30U-F_1x02_P5.0mm_Vertical,C99102,1
Buckdiode,D6,D_SMA,C64982,1
CPT-9019S-SMT,LS2,CUI_CPT-9019S-SMT,C95163,1
Conn_ARM_JTAG_SWD_10,J6,PinHeader_2x05_P1.27mm_Vertical,C2685167,1
D_TVS,D4,D_SOD-882,C18212174,1
Ferrite Bead,BLM18AG601SZ1D1,L_0603_1608Metric,C710353,1
Inductor 6.8uH,L1,L_Coilcraft_XxL4030,C3040663,1
LED,D1,LED_0603_1608Metric,C2286,1
LQG15HS27NJ02D,FB1,L_0402_1005Metric,C12669,1
LSM6DSV320X,U7,LGA-14_3x2.5mm_P0.5mm_LayoutBorder3x4y,C26633007,1
MAX-M10S,U5,ublox_MAX,C24834155,1
MMC5983MA,U4,PQFN50P300X300X100-16N,C404329,1
MS5611-01BA,U2,LGA-8_3x5mm_P1.25mm,C15639,1
Micro_SD_Card_Det2,J9,microSD_HC_Molex_104031-0811,C585350,1
PESD2USB5UX,U11,TSOT-23,C54533312,1
RFD900ux 3 Pin Power Select,J7,CONN_BM03B-GHS-TBT_LF__SN__N_,C161691,1
SM10B-GHS-TB,J5,JST_SM10B-GHS-TB,C2683602,1
SS54,"D5,D7",D_SMA,C22452,2
STM32F407VGTx,U1,LQFP-100_14x14mm_P0.5mm,C12345,1
SW_Push,NRST1,SW_SPST_PTS810,C221895,1
TPS2121,U12,IC_TPS2121RUXR,C2156025,1
TPS54331DR,U13,SOIC127P599X175-8N,C9865,1
U.FL,J4,U.FL_Hirose_U.FL-R-SMT-1_Vertical,C5137195,1
USB_C_Receptacle_USB2.0_16P,J8,USB_C_Receptacle_GCT_USB4105-xx-A_16P_TopMnt_Horizontal,C3020560,1
W25Q128JVS,U10,SOIC-8_5.3x5.3mm_P1.27mm,C97521,1
WS2812B-2020,"D2,D3",LED_WS2812B-2020_PLCC4_2.0x2.0mm,C2976072,2
